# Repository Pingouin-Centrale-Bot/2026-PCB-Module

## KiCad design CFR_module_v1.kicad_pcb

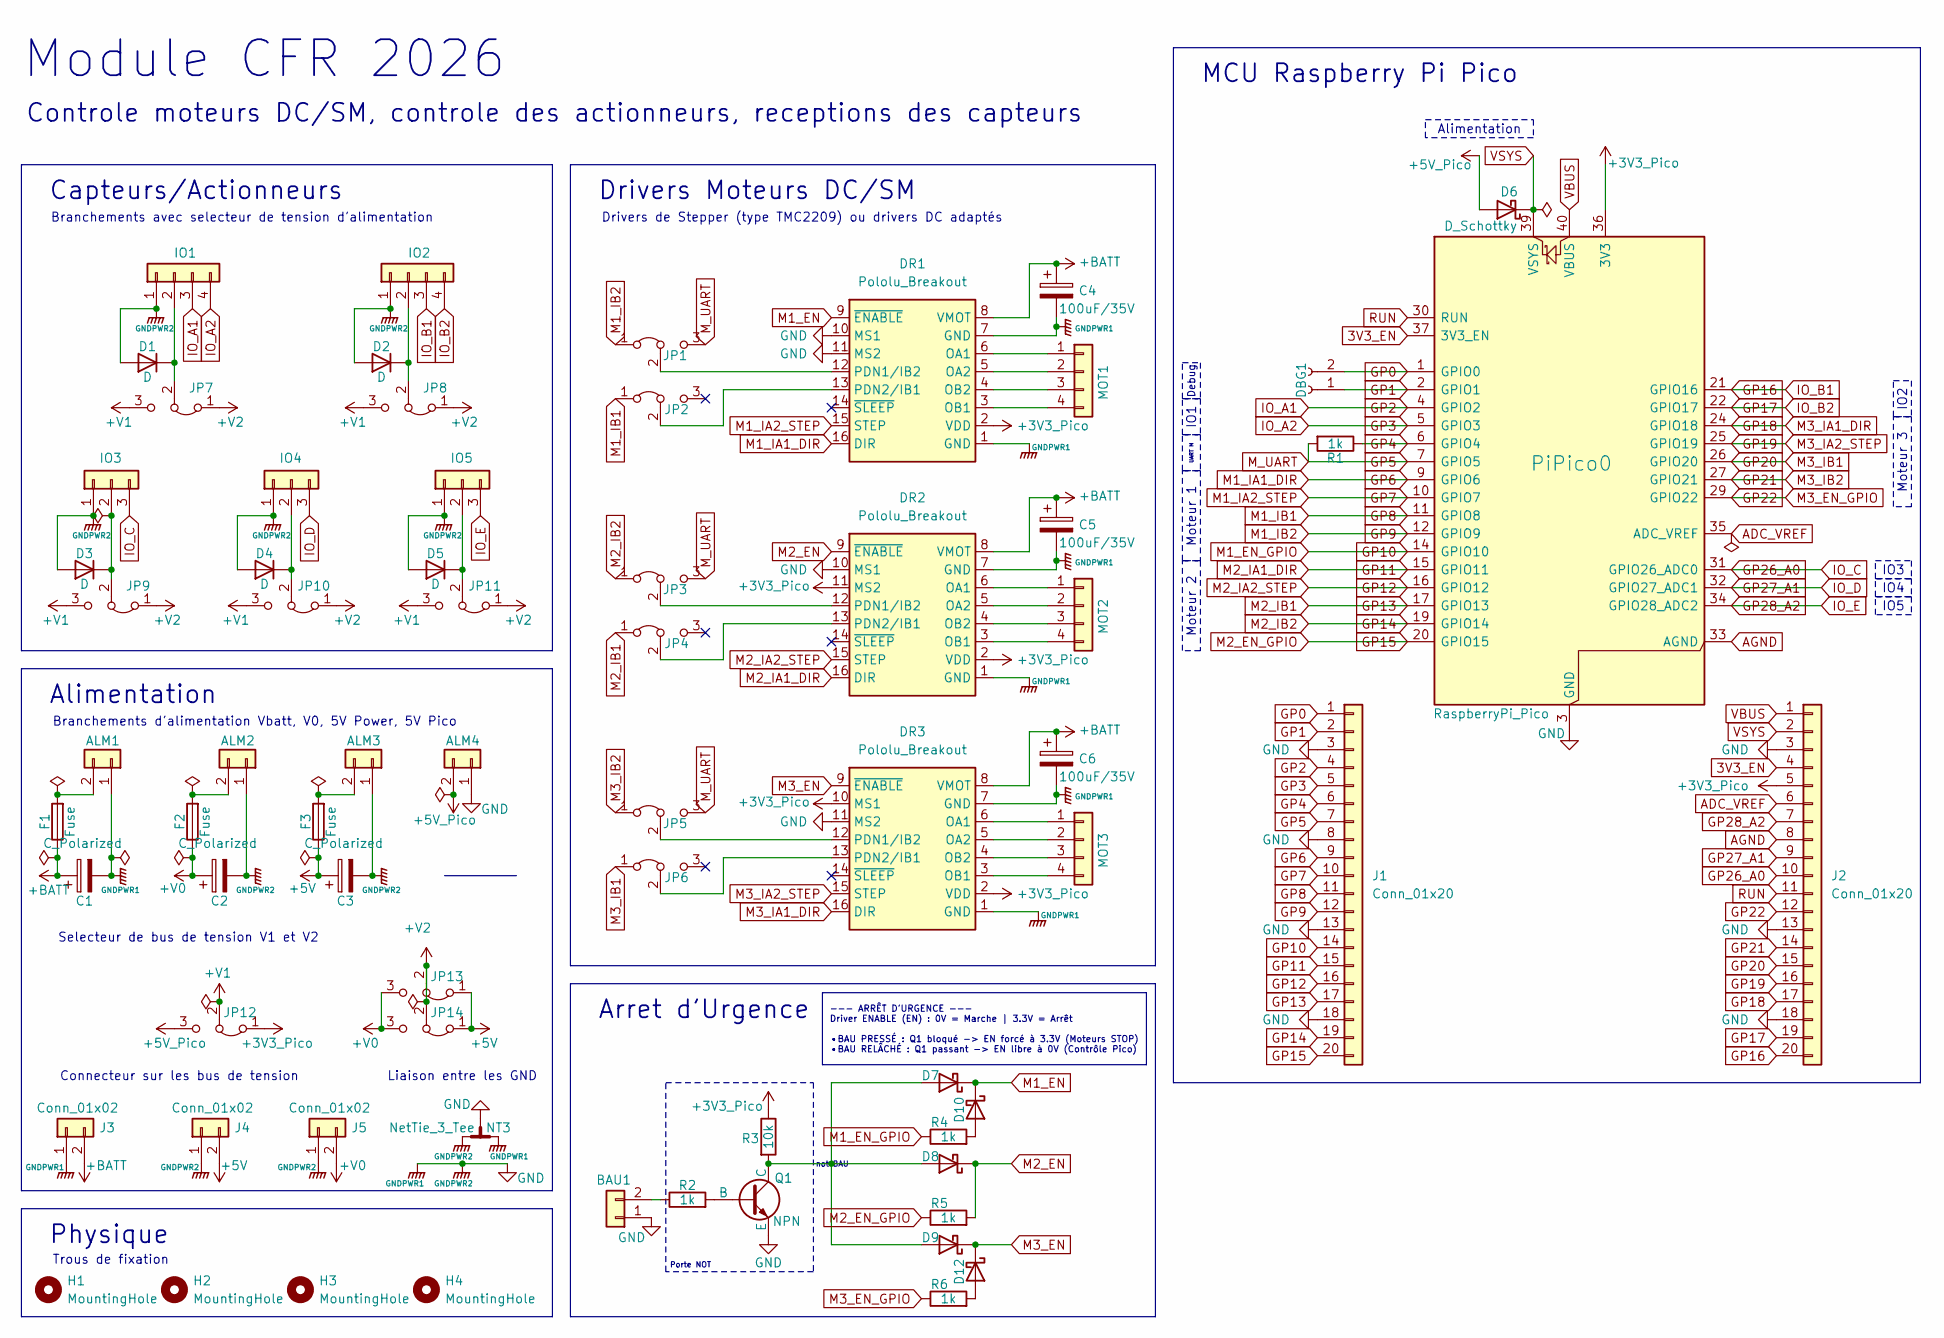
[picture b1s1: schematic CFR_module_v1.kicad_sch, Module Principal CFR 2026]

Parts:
ALM1, ALM2, ALM3, ALM4: Conn_01x02; AMASS_XT30U-F_1x02_P5.0mm_Vertical
BAU1: Conn_01x02; PinHeader_1x02_P2.54mm_Vertical
C1: C_Polarized; CP_Elec_10x10.5
C2: C_Polarized; CP_Elec_8x10
C3: C_Polarized; CP_Elec_6.3x5.8
C4, C5, C6: 100uF/35V; CP_Elec_6.3x7.7
D1, D2, D3, D4, D5: D; D_SMA_Handsoldering
D6, D7, D8, D9, D10, D12: D_Schottky; D_SOD-123
DBG1: Conn_01x02_Socket; PinHeader_1x02_P2.54mm_Vertical
DR1, DR2, DR3: Pololu_Breakout; Pololu_Breakout-16_15.2x20.3mm_Better_Silkscreen
F1, F2, F3: Fuse; Fuse_1206_3216Metric_Pad1.42x1.75mm_HandSolder
H1, H2, H3, H4: MountingHole; MountingHole_3.2mm_M3
IO1, IO2: Conn_01x04; JST_PH_B4B-PH-K_1x04_P2.00mm_Vertical
IO3, IO4, IO5: Conn_01x03; JST_PH_B3B-PH-K_1x03_P2.00mm_Vertical
J1, J2: Conn_01x20; PinSocket_1x20_P2.54mm_Vertical
J3, J4, J5: Conn_01x02; PinHeader_1x02_P2.54mm_Vertical
JP1, JP2, JP3, JP4, JP5, JP6, JP7, JP8, JP9, JP10, JP11, JP12, JP13, JP14: Jumper_3_Bridged12; PinHeader_1x03_P2.54mm_Vertical
MOT1, MOT2, MOT3: Conn_01x04; PinHeader_1x04_P2.54mm_Vertical
NT3: NetTie_3_Tee; NetTie-3_SMD_Pad2.0mm
PiPico0: RaspberryPi_Pico; RaspberryPi_Pico_Common_SMD
Q1: NPN; SOT-23
R1, R2, R4, R5, R6: 1k; R_0805_2012Metric_Pad1.20x1.40mm_HandSolder
R3: 10k; R_0805_2012Metric_Pad1.20x1.40mm_HandSolder

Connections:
3V3_EN: J2.4, PiPico0.37 (3V3_EN)
+3V3_Pico: DR1.2 (VDD), DR2.2 (VDD), DR2.11 (MS2), DR3.2 (VDD), DR3.10 (MS1), J2.5, JP12.1 (A), PiPico0.36 (3V3), R3.1
+5V: C3.1, F3.1, J4.2, JP13.1 (A), JP14.1 (A)
+5V_Pico: ALM4.2, D6.2 (A), JP12.3 (B)
+BATT: C1.1, C4.1, C5.1, C6.1, DR1.8 (VMOT), DR2.8 (VMOT), DR3.8 (VMOT), F1.1, J3.2
+V0: C2.1, F2.1, J5.2, JP13.3 (B), JP14.3 (B)
+V1: JP7.3 (B), JP8.3 (B), JP9.3 (B), JP10.3 (B), JP11.3 (B), JP12.2 (C)
+V2: JP7.1 (A), JP8.1 (A), JP9.1 (A), JP10.1 (A), JP11.1 (A), JP13.2 (C), JP14.2 (C)
ADC_VREF: J2.6, PiPico0.35 (ADC_VREF)
AGND: J2.8, PiPico0.33 (AGND)
GP0: DBG1.2, J1.1, PiPico0.1 (GPIO0)
GP1: DBG1.1, J1.2, PiPico0.2 (GPIO1)
GP2: IO1.3, J1.4, PiPico0.4 (GPIO2)
GP3: IO1.4, J1.5, PiPico0.5 (GPIO3)
GP4: J1.6, PiPico0.6 (GPIO4), R1.1
GP5: J1.7, JP1.3 (B), JP3.3 (B), JP5.3 (B), PiPico0.7 (GPIO5), R1.2
GP6: DR1.16 (DIR), J1.9, PiPico0.9 (GPIO6)
GP7: DR1.15 (STEP), J1.10, PiPico0.10 (GPIO7)
GP8: J1.11, JP2.1 (A), PiPico0.11 (GPIO8)
GP9: J1.12, JP1.1 (A), PiPico0.12 (GPIO9)
GP10: J1.14, PiPico0.14 (GPIO10), R4.1
GP11: DR2.16 (DIR), J1.15, PiPico0.15 (GPIO11)
GP12: DR2.15 (STEP), J1.16, PiPico0.16 (GPIO12)
GP13: J1.17, JP4.1 (A), PiPico0.17 (GPIO13)
GP14: J1.19, JP3.1 (A), PiPico0.19 (GPIO14)
GP15: J1.20, PiPico0.20 (GPIO15), R5.1
GP16: IO2.3, J2.20, PiPico0.21 (GPIO16)
GP17: IO2.4, J2.19, PiPico0.22 (GPIO17)
GP18: DR3.16 (DIR), J2.17, PiPico0.24 (GPIO18)
GP19: DR3.15 (STEP), J2.16, PiPico0.25 (GPIO19)
GP20: J2.15, JP6.1 (A), PiPico0.26 (GPIO20)
GP21: J2.14, JP5.1 (A), PiPico0.27 (GPIO21)
GP22: J2.12, PiPico0.29 (GPIO22), R6.1
GP26_A0: IO3.3, J2.10, PiPico0.31 (GPIO26_ADC0)
GP27_A1: IO4.3, J2.9, PiPico0.32 (GPIO27_ADC1)
GP28_A2: IO5.3, J2.7, PiPico0.34 (GPIO28_ADC2)
M1_EN: D7.1 (K), D10.1 (K), DR1.9 (~ENABLE)
M3_EN: D9.1 (K), D12.1 (K), DR3.9 (~ENABLE)
unnamed: ALM1.2, F1.2
unnamed: ALM2.2, F2.2
unnamed: ALM3.2, F3.2
unnamed: BAU1.2, R2.1
unnamed: D1.1 (K), IO1.2, JP7.2 (C)
unnamed: D2.1 (K), IO2.2, JP8.2 (C)
unnamed: D3.1 (K), IO3.2, JP9.2 (C)
unnamed: D4.1 (K), IO4.2, JP10.2 (C)
unnamed: D5.1 (K), IO5.2, JP11.2 (C)
unnamed: D7.2 (A), D8.2 (A), D9.2 (A), Q1.1 (C), R3.2
unnamed: D10.2 (A), R4.2
unnamed: D12.2 (A), R6.2
unnamed: DR1.6 (OA1), MOT1.1
unnamed: DR1.5 (OA2), MOT1.2
unnamed: DR1.3 (OB1), MOT1.4
unnamed: DR1.4 (OB2), MOT1.3
unnamed: DR1.12 (PDN1/IB2), JP1.2 (C)
unnamed: DR1.13 (PDN2/IB1), JP2.2 (C)
unnamed: DR2.6 (OA1), MOT2.1
unnamed: DR2.5 (OA2), MOT2.2
unnamed: DR2.3 (OB1), MOT2.4
unnamed: DR2.4 (OB2), MOT2.3
unnamed: DR2.12 (PDN1/IB2), JP3.2 (C)
unnamed: DR2.13 (PDN2/IB1), JP4.2 (C)
unnamed: DR3.6 (OA1), MOT3.1
unnamed: DR3.5 (OA2), MOT3.2
unnamed: DR3.3 (OB1), MOT3.4
unnamed: DR3.4 (OB2), MOT3.3
unnamed: DR3.12 (PDN1/IB2), JP5.2 (C)
unnamed: DR3.13 (PDN2/IB1), JP6.2 (C)
unnamed: Q1.2 (B), R2.2
RUN: J2.11, PiPico0.30 (RUN)
VBUS: J2.1, PiPico0.40 (VBUS)
VSYS: D6.1 (K), J2.2, PiPico0.39 (VSYS)

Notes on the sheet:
MCU Raspberry Pi Pico
Physique
Controle moteurs DC/SM, controle des actionneurs, receptions des capteurs
Trous de fixation
Module CFR 2026
Porte NOT
Drivers Moteurs DC/SM
Selecteur de bus de tension V1 et V2
Drivers de Stepper (type TMC2209) ou drivers DC adaptés
Capteurs/Actionneurs
not BAU
Connecteur sur les bus de tension
Alimentation
Branchements d'alimentation Vbatt, V0, 5V Power, 5V Pico
Branchements avec selecteur de tension d'alimentation
Arret d'Urgence
Liaison entre les GND
Moteur 2
--- ARRÊT D'URGENCE --- Driver ENABLE (EN) : 0V = Marche | 3.3V = Arrêt •BAU PRESSÉ : Q1 bloqué -> EN forcé à 3.3V (Moteurs STOP) •BAU RELÂCHÉ : Q1 passant -> EN libre à 0V (Contrôle Pico)
IO5
Moteur 1
IO1
IO4
Moteur 3
IO2
UART M
IO3
Debug

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
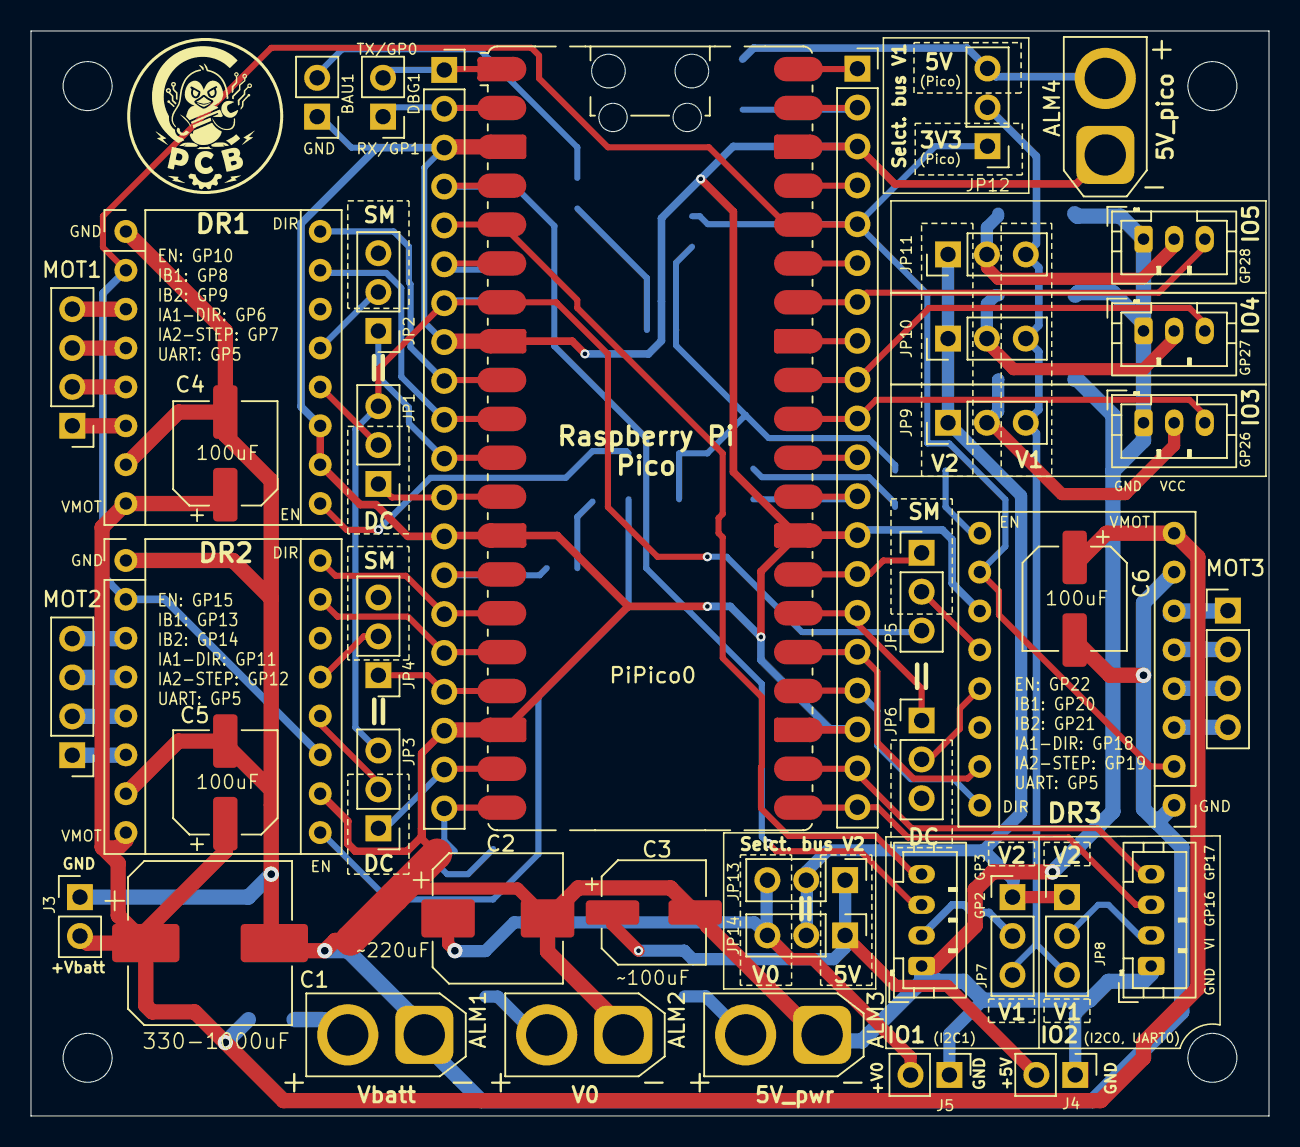
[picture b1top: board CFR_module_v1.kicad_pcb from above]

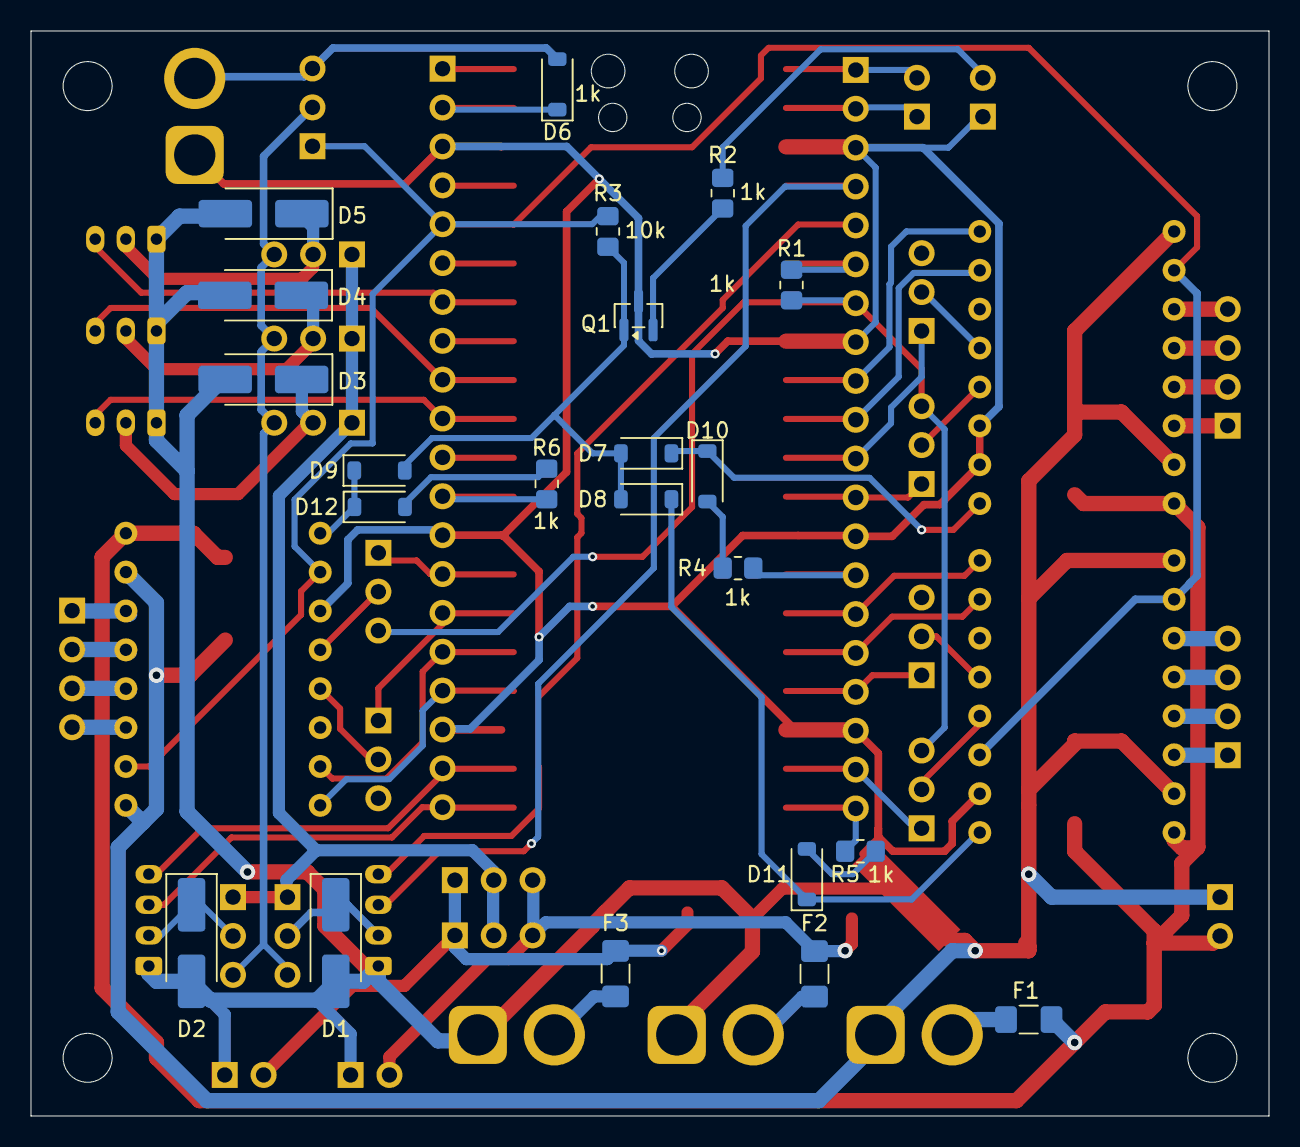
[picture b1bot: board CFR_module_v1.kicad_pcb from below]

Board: 2 copper layers, 80.9 x 70.9 mm, 70 parts (22 on the bottom side), 77 nets.

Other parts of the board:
D11: D_Schottky; D_SOD-123

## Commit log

2026-03-12 ajout de tous les fichiers
2026-03-12 Test commit depuis Kicad
2026-03-12 Test de commit/push depuis kicad
2026-03-19 Modifs
2026-03-19 Ajout du dossier de la librairie Custom
2026-03-20 v1 du schematics, debut de pcb
2026-03-20 pcb ok
2026-03-21 fini avant modifs
2026-03-21 GND commun et ajout de branchements batterie
2026-03-21 liste des composants
2026-03-21 Ajout de la mention (Pico) sur le selectionneur V1
2026-03-21 Suppression des REF J1 J2
2026-03-21 Update des footprints pour supprimer les warnings du DRC
2026-03-22 ajout d'explication sur schematics
2026-03-28 Placement composant front et silkscreen
